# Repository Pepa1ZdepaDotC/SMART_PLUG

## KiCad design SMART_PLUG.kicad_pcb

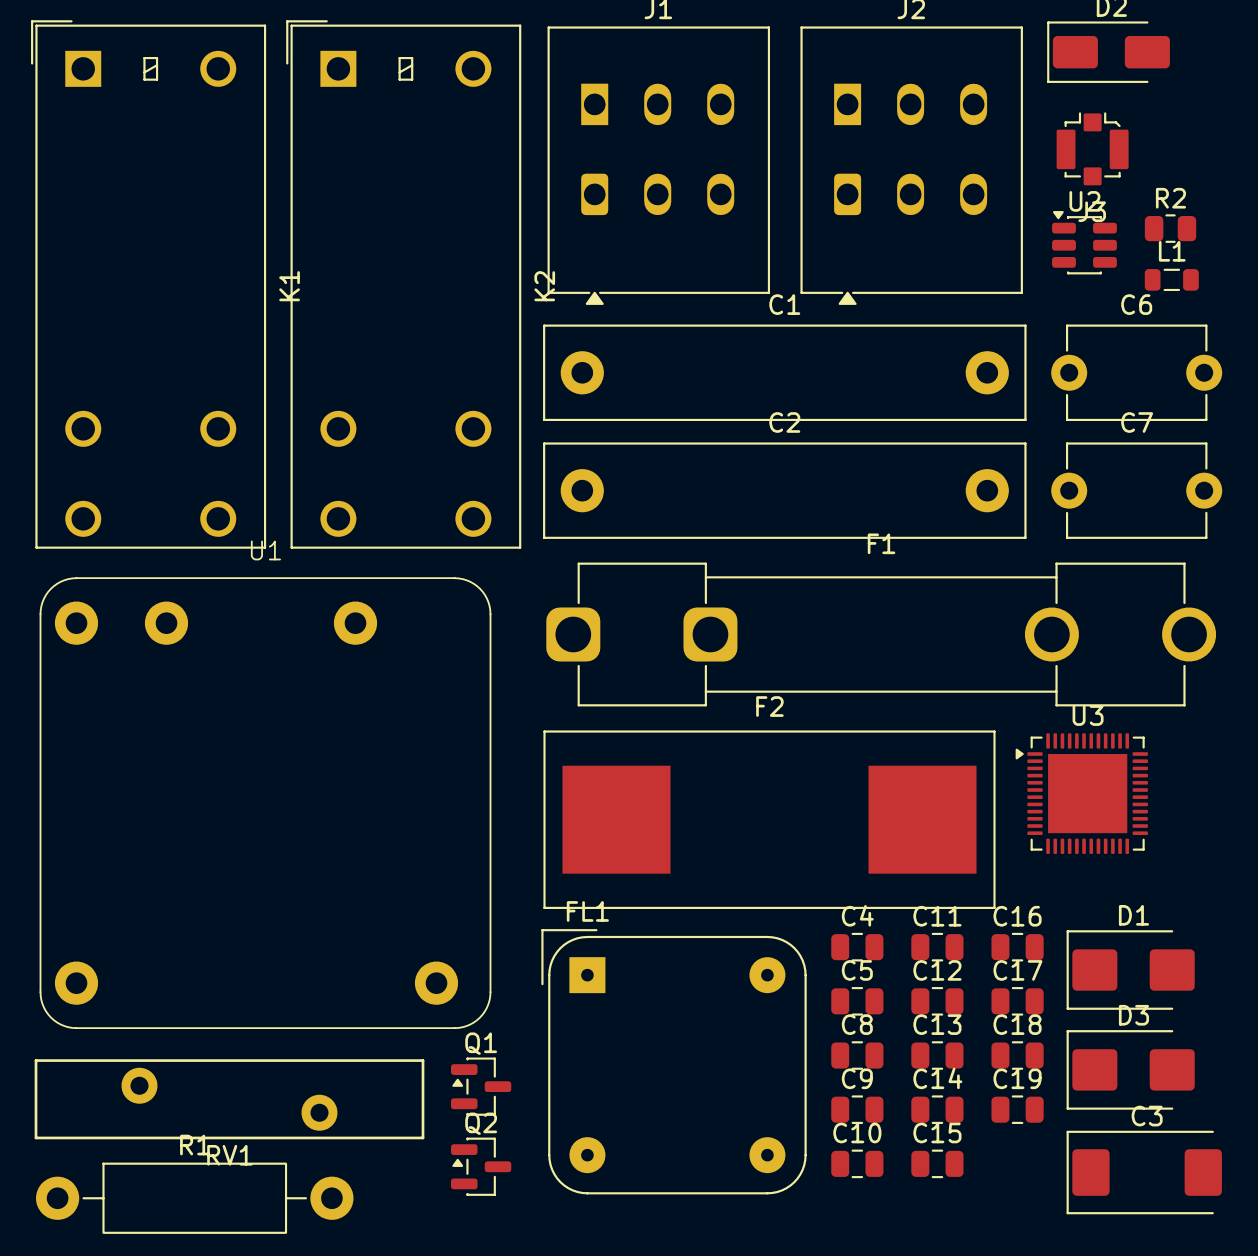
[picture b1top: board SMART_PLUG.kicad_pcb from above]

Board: 2 copper layers, 39 parts (0 on the bottom side), 20 nets, no tracks yet.

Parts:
C1, C2: 470nF; C_Rect_L26.5mm_W5.0mm_P22.50mm_MKS4
C3: 100uF; CP_EIA-7343-31_Kemet-D
C4, C5, C9, C10, C11, C12, C13: 10uF; C_0805_2012Metric
C6, C7: 2.2nF; C_Disc_D7.5mm_W5.0mm_P7.50mm
C8: 100nF; C_0805_2012Metric
C14, C15, C16, C17, C18, C19: 1uF; C_0805_2012Metric
D1, D3: B240; D_SMB
D2: SMAJ12A; D_SMA
F1: ZGTH-10A; Fuseholder_Clip-6.3x32mm_Littelfuse_102_122_Inline_P34.21x7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
F2: TSD-100MA; Fuseholder_Cylinder-5x20mm_Wuerth_696103101002-SMD_Horizont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
FL1: Choke_Schaffner_RN102-0.3-02-12M; Choke_Schaffner_RN102-04-14.0x14.0mm
J1, J2: WAGO 2601-1103; TerminalBlock_WAGO_2601-1103_1x03_P3.50mm_Horizontal
J3: U.FL; U.FL_Molex_MCRF_73412-0110_Vertical
K1, K2: G2RL-1A-E; Relay_SPST_Omron_G2RL-1A-E
L1: 10uF; L_0805_2012Metric
Q1, Q2: AO3400A; SOT-23
R1: 500K; R_Axial_DIN0411_L9.9mm_D3.6mm_P15.24mm_Horizontal
R2: 100K; R_0805_2012Metric
RV1: SIOV-S20K275; RV_Disc_D21.5mm_W4.3mm_P10mm
U1: ZP05S1200WB; ZP03S1200WE
U2: AP63203WU; TSOT-23-6
U3: NRF52840-QFAA-F-R; QFN-48-1EP_6x6mm_P0.4mm_EP4.4x4.4mm

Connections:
+3.3V: C14.1, C15.1, C16.1, C17.1, U3.12 (VDD), U3.17 (VDD), U3.25 (VDD), U3.37 (VDD), U3.48 (VDD)
+12V: C3.1, C4.1, C5.1, C9.1, D1.1 (K), D2.1 (A1), D3.1 (K), K1.A1, K2.A1, R2.1, U1.3 (V_{OUT}), U2.2 (EN), U2.3 (IN)
/ANT: C18.1, U3.31 (ANT)
/ANT_LC: C19.1, J3.1 (In)
/BST: C8.2, U2.6 (BST)
/DEC4_6: U3.33 (DEC6), U3.46 (DEC4)
/REL1: D1.2 (A), K1.A2, Q1.3 (D)
/REL2: D3.2 (A), K2.A2, Q2.3 (D)
/SW: C8.1, L1.1, U2.5 (SW)
Earth_Protective: C6.2, C7.2, J1.2, J2.2
GND: C3.2, C4.2, C5.2, C9.2, C10.2, C11.2, C12.2, C13.2, C14.2, C15.2, C16.2, C17.2, C18.2, C19.2, D2.2 (A2), J3.2 (Ext), Q1.2 (S), Q2.2 (S), R2.2, U1.4 (GND), U2.4 (GND), U3.32 (VSS_PA), U3.45 (VSS)
unnamed: C1.1, F2.2, FL1.1, R1.1
unnamed: F1.2, F2.1, K1.14, RV1.1
unnamed: F1.1, J1.1
unnamed: C1.2, FL1.3, J1.3, K2.14, R1.2, RV1.2
unnamed: J2.1, K2.13
unnamed: J2.3, K1.13
unnamed: C2.1, C6.1, FL1.2, U1.2 (L)
unnamed: C2.2, C7.1, FL1.4, U1.1 (N)
unnamed: C10.1, C11.1, C12.1, C13.1, L1.2, U2.1 (FB)

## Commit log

2026-06-12 Add files via upload
    kicad commit
